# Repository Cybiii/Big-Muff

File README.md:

# Big Muff

<p align="center">
    <a href="https://www.sebastiansebs.com/BigMuff/BigMuff.pdf">📄 View Schematic PDF</a>
</p>

## Overview

This project describes a custom-designed **Big Muff** guitar effects pedal, built using discrete components. This four-stage analog circuit provides powerful signal amplification, harmonic distortion, and tone shaping capabilities.

The circuit features four **NPN 2N2222 transistors** configured in distinct stages: an input buffer, two gain/clipping stages, a passive tone control section, and an output buffer with volume control. The design incorporates silicon diodes for controlled signal clipping and a comprehensive network of resistors and capacitors for optimal signal processing and tone shaping.

<p align="center">
    
    <p align="center">Figure 1: Front view of the PCB</p>
</p>

<p align="center">
    
    <p align="center">Figure 2: Back view of the PCB</p>
</p>

## Project Architecture

The project is structured hierarchically within KiCad, with the following key sections:

1.  **Root:** The top-level schematic, connecting the main circuit blocks.
2.  **Project Architecture:** Defines the overall system architecture and contains the complete Big Muff circuit.
    - **Input Buffer Stage (Q1):** High-impedance input for guitar signal
    - **First Gain/Clipping Stage (Q2):** Primary amplification and distortion
    - **Second Gain/Clipping Stage (Q3):** Additional gain and harmonic saturation
    - **Tone Control:** Passive filter network for frequency shaping
    - **Output Buffer Stage (Q4):** Final amplification and volume control

## Circuit Analysis

Based on the schematic, here's a breakdown of each section of the Big Muff circuit:

### Section 1: Input Buffer / Pre-Amplifier (Q1)

- **Function:** This stage acts as a high-impedance input buffer and pre-amplifier. The large input resistors help present a high input impedance to the guitar signal, preventing loading of the guitar's pickups. Q1 amplifies the incoming signal while the supporting network provides frequency shaping and stability.

### Section 2.1: First Gain/Clipping Stage (Q2)

- **Function:** This is a key gain and clipping stage. Q2 provides significant amplification, and the diodes D1 and D2 are placed in a feedback configuration to clip the amplified signal when it reaches a certain voltage threshold, producing the characteristic Big Muff distortion and sustain.

### Section 2.2: Second Gain/Clipping Stage (Q3)

- **Function:** This stage provides further amplification and clipping. The signal from Q2 is fed into Q3, which amplifies it even more. Diodes D3 and D4 perform another round of signal clipping, contributing to the heavy, saturated distortion sound characteristic of the Big Muff.

### Section 3: Tone Control (Passive Network)

- **Function:** This is the passive "Tone" control section, a hallmark of the Big Muff. It's a variable filter that allows you to sweep between more bass-heavy (less treble) and more treble-heavy (less bass) sounds. The specific capacitor values determine the frequencies affected by the tone control.

### Section 4: Output Buffer / Volume Control (Q4)

- **Function:** This final stage acts as an output buffer and incorporates the master volume control. Q4 provides a final stage of amplification and buffering to drive the output effectively. The volume control allows adjustment of the overall loudness of the distorted signal before it leaves the pedal.

## PCB Layers

The PCB is meticulously designed with the following **4 layers** to optimize **signal integrity**, **power delivery networks**, and **component density**, ensuring robust performance and manufacturability:

1.  **Layer Top (F.Cu - Front Copper):**

    - **Description:** This is the primary **component placement layer**, accommodating **Surface Mount Devices** and **through-hole components**. It's strategically utilized for **critical signal routing**, **component interconnections**, and minimizing trace lengths for optimal **signal integrity**.

<p align="center">
    
    <p align="center">Figure 3: Top copper layer showing component placement and primary routing</p>
</p>

2.  **Power Layer (In1.Cu - Inner Copper 1):**

    - **Description:** A dedicated **internal power plane** for the **+9V rail**. This continuous copper plane ensures **low-impedance power distribution**, minimizing **voltage ripple** and providing a stable current source across the entire board, critical for **power integrity** of the analog circuitry.

<p align="center">
    
    <p align="center">Figure 4: Internal power plane for stable 9V power delivery network</p>
</p>

3.  **Ground Layer (In2.Cu - Inner Copper 2):**

    - **Description:** A comprehensive **internal ground plane**. This solid plane serves as a universal **low-impedance return path** for all signals, significantly reducing **electromagnetic interference (EMI)**, enhancing **electromagnetic compatibility**, and providing effective **shielding** for sensitive audio traces.

<p align="center">
    
    <p align="center">Figure 5: Internal ground plane serving as robust ground reference and EMI shield</p>
</p>

4.  **Layer Bottom (B.Cu - Bottom Copper):**

    - **Description:** Utilized for completing **signal routing**, particularly for connections requiring longer runs or bypassing components. This layer also provides flexibility for **additional component placement** and routing optimization.

<p align="center">
    
    <p align="center">Figure 6: Bottom copper layer showing secondary routing and connections</p>
</p>

## Key Components

- **Q1, Q2, Q3, Q4:** 2N2222 NPN Transistors (TO-18 or TO-92 package)
- **D1, D2, D3, D4:** 1N914 Silicon Diodes for signal clipping
- **Various Resistors:** Carbon film or metal film for bias, load, and feedback
- **Capacitors:** Mix of electrolytic, film, and ceramic types for different functions
- **Potentiometers:** Volume and Tone controls (typically 100kΩ)

## For Larger Capacitance Values (e.g., 1μF):

We typically utilize **electrolytic capacitors**. These are commonly used for coupling between stages and for power supply filtering due to their high capacitance in a relatively small form factor. **Important:** Electrolytic capacitors are **polarized**, meaning they must be installed with the correct orientation (positive lead to higher voltage, negative lead to lower voltage/ground) to prevent damage.

## Important Files

- `Big Muff.kicad_pro`: KiCad project file
- `Big Muff.kicad_sch`: Top-level schematic
- `Project Architecture.kicad_sch`: Complete circuit schematic
- `Revision History.kicad_sch`: Project revision tracking
- `Big Muff.kicad_pcb`: PCB layout file
- `Big Muff.kicad_dru`: PCB design rules file
- `Big Muff.kicad_prl`: Project-specific library settings
- `Schematic/BigMuff.pdf`: Complete schematic in PDF format

## Design Features

- **Four-stage analog signal processing**
- **Symmetrical diode clipping for rich harmonic distortion**
- **Passive tone control for frequency shaping**
- **High input impedance for guitar compatibility**
- **Low output impedance for driving amplifiers**
- **Through-hole components for easy assembly and modification**
- **Four-layer PCB design for optimal signal integrity**
- **Professional PCB layout with proper grounding and power distribution**

This Big Muff implementation provides the classic thick, creamy distortion that has made this circuit a favorite among guitarists for decades, while using modern PCB design practices for reliable performance and easy construction.

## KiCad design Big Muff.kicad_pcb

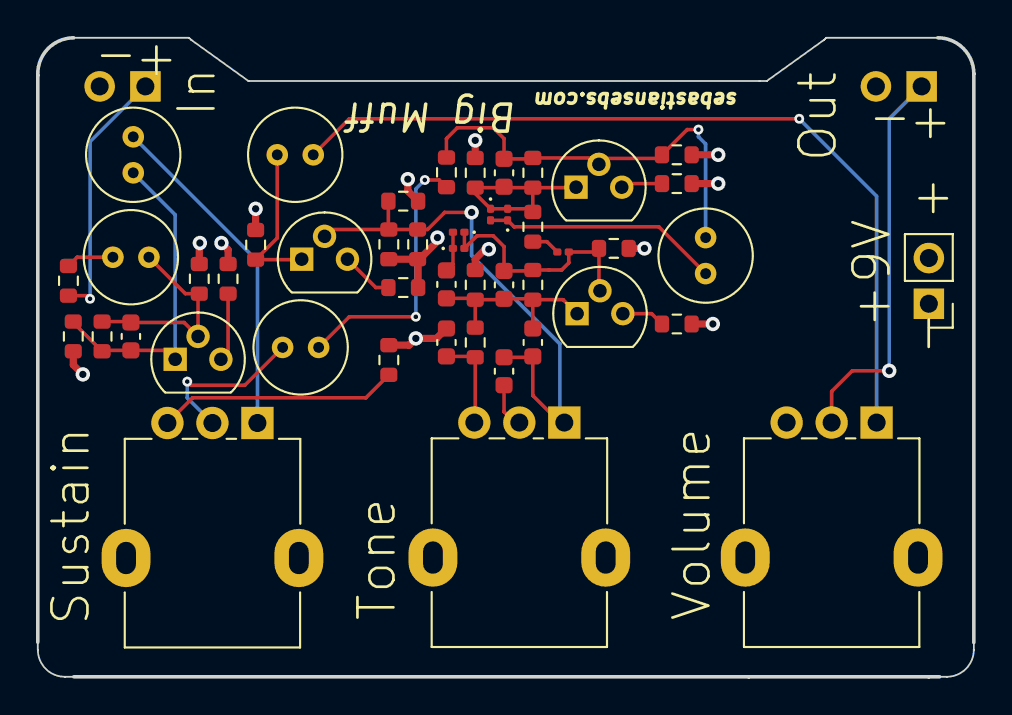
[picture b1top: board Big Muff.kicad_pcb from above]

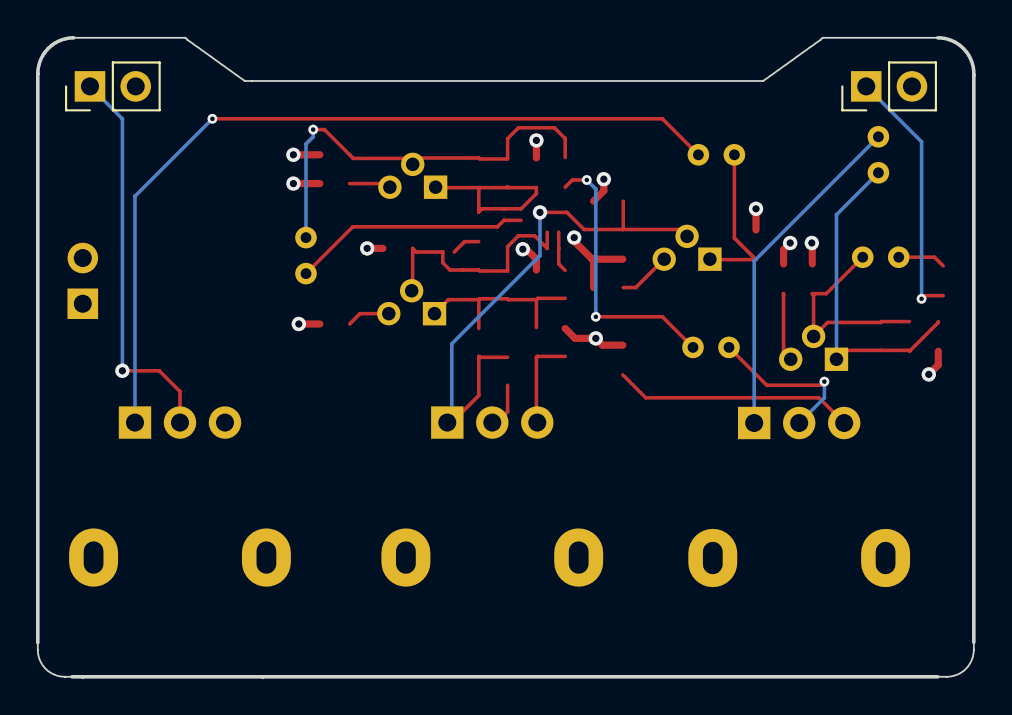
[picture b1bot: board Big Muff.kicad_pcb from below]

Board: 4 copper layers, 52.0 x 35.5 mm, 49 parts (2 on the bottom side), 27 nets.

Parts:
C1, C3, C6, C8, C14: 1uF; C_Radial_D5.0mm_H7.0mm_P2.00mm
C2, C5, C9: 470pF; C_0603_1608Metric
C10, C12: 0.1uF; C_0603_1608Metric
C11: 0.0033uF; C_0603_1608Metric
C13: 0.047uF; C_0603_1608Metric
C15: 0.1uF; C_0201_0603Metric
D1, D2, D3, D4: 1N914; D_0201_0603Metric
J2, J3, J4: 9V; PinHeader_1x02_P2.54mm_Vertical
Q1, Q2, Q3, Q4: 2N2222; TO-92
R1, R17: 33k; R_0603_1608Metric
R2: R; R_0603_1608Metric
R3, R11, R16: 16k; R_0603_1608Metric
R4, R9, R14, R20: 100k; R_0603_1608Metric
R6: 1k; R_0603_1608Metric
R7, R12, R22: 10k; R_0603_1608Metric
R8, R13, R19: 476k; R_0603_1608Metric
R10, R15, R23: 100; R_0603_1608Metric
R18: 22k; R_0603_1608Metric
R21: 1.6k; R_0603_1608Metric
RV1: Sustain; Potentiometer_Alpha_RD901F-40-00D_Single_Vertical
RV2: Tone; Potentiometer_Alpha_RD901F-40-00D_Single_Vertical
RV3: Volume; Potentiometer_Alpha_RD901F-40-00D_Single_Vertical

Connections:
9V: J3.1, R3.2, R11.1, R16.1, R19.1, R22.1
B1: C1.1, C2.1, Q1.B1, R2.2, R4.1
B2: C5.1, C6.1, Q2.B2, R7.1, R8.2, R9.1
B3: C9.1, C15.2, D3.2 (A), D4.1 (K), Q3.B3, R13.2, R14.1
B4: C11.2, C12.2, Q4.B4, R18.1, R19.2, R20.1, RV2.1
C1: C2.2, C3.1, Q1.C1, R2.1, R3.1
C2: C5.2, D1.1 (K), D2.2 (A), Q2.C2, R8.1, R11.2, R12.1
C3: C9.2, C10.2, C11.1, Q3.C3, R13.1, R16.2, R17.2
C4: C8.1, Q4.C4, R22.2
E1: Q1.E1, R23.1
E2: Q2.E2, R10.1
E3: Q3.E3, R15.1
E4: Q4.E4, R21.1
GND: C13.1, J2.2, J3.2, J4.2, R4.2, R6.2, R9.2, R10.2, R14.2, R15.2, R18.2, R20.2, R21.2, R23.2, RV3.3
IN: J2.1, R1.1
unnamed: C1.2, R1.2
unnamed: C3.2, RV1.1
unnamed: C8.2, RV3.1
unnamed: C12.1, RV2.2
unnamed: C13.2, R17.1, RV2.3
unnamed: C14.1, R7.2
unnamed: C14.2, RV1.2
unnamed: C15.1, R12.2
unnamed: C6.2, D1.2 (A), D2.1 (K)
unnamed: C10.1, D3.1 (K), D4.2 (A)
unnamed: R6.1, RV1.3
OUT: J4.1, RV3.2

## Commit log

2025-06-24 KiCad schematic
2025-06-24 Readme
2025-06-24 ksajdhajd
